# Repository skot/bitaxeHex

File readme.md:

Warning: the bitaxeHex is unfinished. there may be hardware and firmware bugs. Please see The bitaxeHex channel on the [OSMU Discord](https://discord.gg/osmu) for the latest status

> Closed Source is Antithetical to Bitcoin

# Presenting: The bitaxeHex
bitaxeHex is a follow on to the [bitaxe](https://github.com/skot/bitaxe) that incorporates six BM1366 ASICs from the Antminer S19XP

## Goals
- **Standalone**: can mine directly to your pool over WiFi. No External computer needed.
- **Embedded**: low cost, low maintenance, high availability, high reliability, low power.
- **ASIC**: based on the very efficient BM1366 from Bitmain.
- **Versatile**: solo/pool mining, autotune power/heat/efficiency.
- **Open Source**: All design files are provided.

## Features
- **ESP32-S3-WROOM-1** wifi microcontroller on board
- **TI TPS546D24ARVFR** buck regulator steps down the 12V input to power the chain of BM1366
- **TMP1075** measures inlet and outlet PCB temperature.
- **Microchip EMC2302** Controls dual fans
- Header for optional status LCD

## BM1366
- The BM1366 is a undocumented SHA256 mining ASIC from Bitmain. It's mostly used in the Antminer S19XP and S19K Pro
- Bitmain claims the BM1366 has 21.5 W/TH efficiency
- The BM1366 is available (new) for around $15 each.

## Current Status
- v304 This is going to be the official release candidate, but boards have not been produced yet, this version is not final.
- Power draw is around 50W @12V.
- ESP32 miner firmware will configure the power supply to run at the proper voltage.
- This is an _advanced_ build! If you don't have experience building boards, you should probably go build a single ASIC bitaxe first to get the technique down.

## Notes
- Beware that overclocking doesn't produce a higher hash rate on this board, it only causes more heat generation.
- If you decide to build a pre-release board, be sure to order 2 oz. copper on both the internal and external layers.
- The recommended heatsink is not anodized and very conductive on all surfaces. This _should_ be OK as the ASIC tops are not known to be conductive, but this needs some more investigation.

## Revision List
- v304 is a work in progress, some capacitor changes, additional features
- v303 has some improvements in the layout and the 33R inline resistors have been removed.
- V302 is the current working version of this board.  If you want to build this, pull down this git tag.
- V301 does not work, the power supply maintains voltage, but overheats in a drastic way
- V300 does not work, the power supply cannot maintain voltage when a load is applied

## Hardware
- [BM1366 from NBTC on AliExpress](https://www.aliexpress.us/item/3256803471845503.html). Both the `AL` and `AG` variants have been known to work.
- [Heatsink](https://www.aliexpress.us/item/3256805608902122.html) 90mm long variant. This will need to have threaded M3 mounting holes added. See the KiCad board file for the pattern
- [Fans](https://www.amazon.com/Noctua-NF-A8-PWM-Premium-Quiet/dp/B00NEMG62M) At least one 80x80mm 12V 4-pin fan. Like the Noctua NF-A8 PWM. Possibly two.
- [Enclosure](https://www.aliexpress.us/item/3256806064761702.html) (several sellers) 130mm long variant. The bitaxeHex needs to be run inside an enclosure to force air through the heatsink and effectively cool the BM1366s
- The TPS546 can potentially benefit from a [small self-adhesive heatsink](https://www.amazon.com/gp/product/B093V6RK58/) on the top of the package.
- All of the parts on the board are listed in the KiCad BOM

## Software
- [ESP-Miner-multichip](https://github.com/bitaxeorg/esp-miner-multichip) a fork of esp-miner to support multiple ASICs like on the bitaxeHex.

## Power Supply Requirements
- bitaxeHex takes 12V DC input via screw terminals. Power supply should be capable of 100W
  - This [120W Brick](https://www.amazon.com/gp/product/B07PWZQ33N) technically works, but gets a little warmer than it should. You'll need to change the end.
  - 12V 15A 110V AliExpress [Bare PSU](https://www.aliexpress.us/item/3256805439916551.html)

## Building
- Check out [building.md](building.md) for PCB ordering tips
- Check out [assembly.md](assembly.md) for assembly tips

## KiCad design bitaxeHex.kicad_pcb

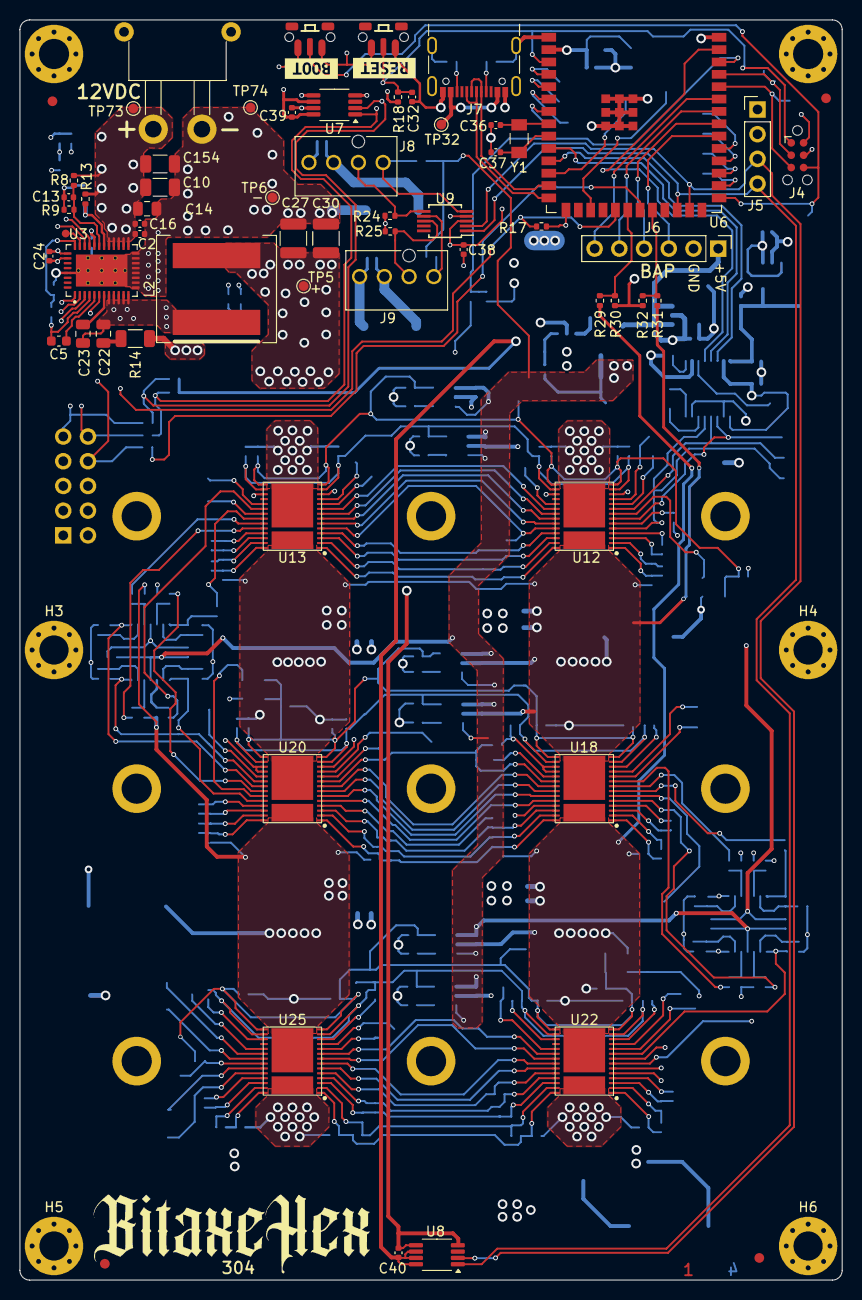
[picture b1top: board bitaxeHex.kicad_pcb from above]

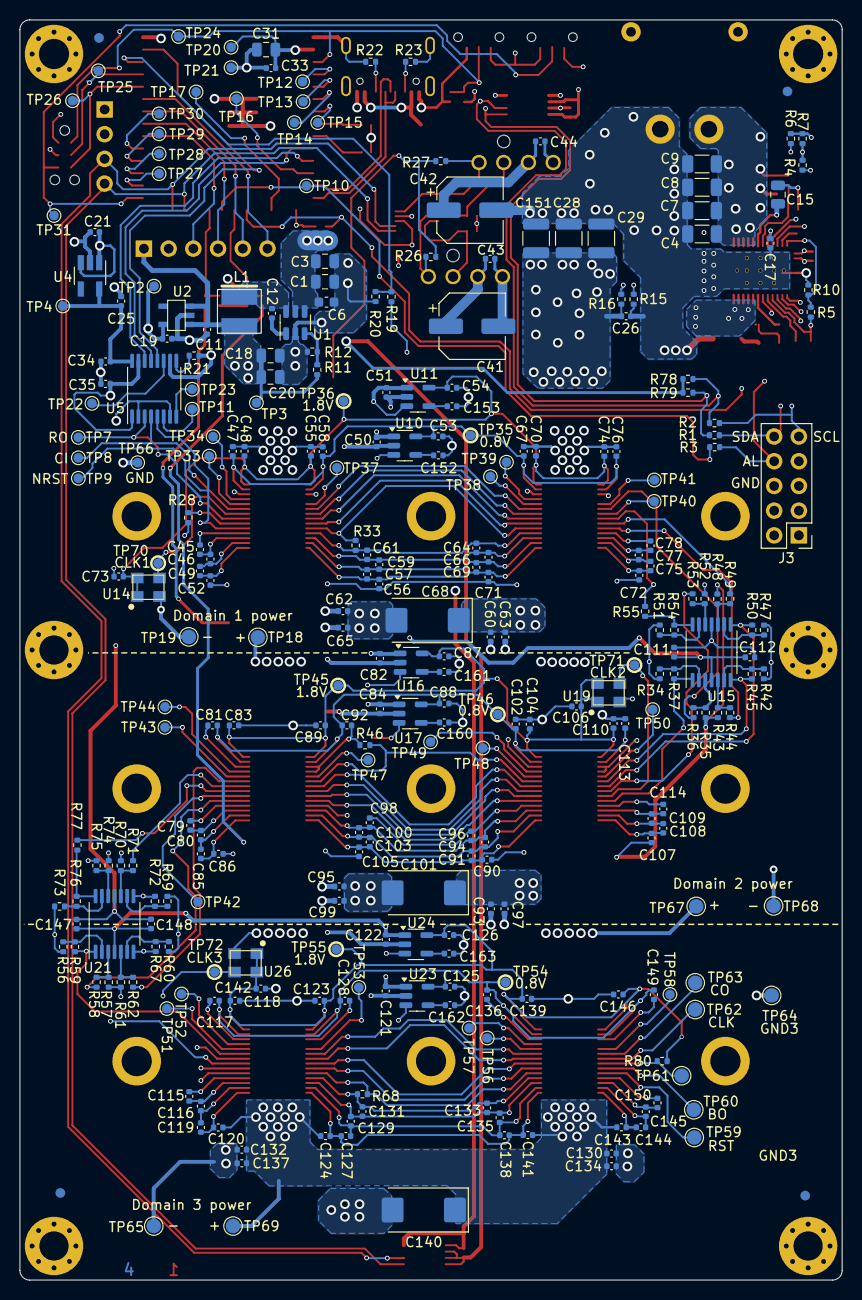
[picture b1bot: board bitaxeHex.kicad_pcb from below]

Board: 4 copper layers, 84.5 x 129.5 mm, 369 parts (289 on the bottom side), 191 nets.

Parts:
C1, C3, C18, C20, C31: 10uF; C_0805_2012Metric
C2: 4.7nF; C_0402_1005Metric
C4, C7, C8, C10: 22uF; C_1206_3216Metric
C5: 1uF; C_0603_1608Metric
C6: 0.1uF; C_0603_1608Metric
C9, C154: 47uF; C_1206_3216Metric
C11, C19, C21, C25, C32, C45, C46, C47, C48, C49, C52, C53, C54, C55, C56, C57, C58, C59, C61, C63, C64, C65, C66, C67, C69, C70, C71, C72, C74, C75, C76, C77, C78, C79, C80, C81, C83, C85, C86, C87, C88, C89, C90, C91, C92, C94, C96, C97, C98, C99, C100, C102, C103, C104, C105, C107, C108, C109, C110, C112, C113, C114, C115, C116, C117, C118, C119, C120, C123, C124, C125, C126, C127, C128, C129, C131, C133, C134, C135, C136, C137, C138, C139, C141, C143, C144, C145, C146, C148, C149, C150: 1uF; C_0402_1005Metric
C12, C33, C50, C51, C60, C62, C73, C82, C84, C93, C95, C106, C111, C121, C122, C130, C132, C142, C147: 0.1uF; C_0402_1005Metric
C13: 100nF; C_0402_1005Metric
C14, C15: 1uF; C_0805_2012Metric
C16, C26: 2.2nF; C_0402_1005Metric
C17: 4.7uF; C_0402_1005Metric
C22: 1nF; C_0805_2012Metric
C23: 100nF; C_0805_2012Metric
C24: 100pF; C_0402_1005Metric
C27, C28, C29: 47uF; C_1210_3225Metric
C30, C151: 100uF; C_1210_3225Metric
C34, C35, C38, C39, C40, C43, C44: 311-3342-1-ND; C_0402_1005Metric
C36, C37: 6.8pF; C_0402_1005Metric
C41, C42: 220uF; CP_Elec_6.3x7.7
C68, C101, C140: 330uF; CP_EIA-7343-31_Kemet-D_Pad2.25x2.55mm_HandSolder
C152, C153, C160, C161, C162, C163: 0.01uF; C_0402_1005Metric
FID1, FID2, FID3, FID4, FID5, FID6, FID7, FID8: Fiducial; Fiducial_1mm_Mask2mm
H1, H2, H3, H4, H5, H6: MountingHole; MountingHole_3mm_Pad_Via
H7, H8, H9, H10, H11, H12, H13, H14, H15: HeatsinkMountingHole; 3.1mm_mounting
HS1: Heatsink; hex-heatsink
J1: XT30; XT30PW-M
J3: Conn_02x05_Odd_Even; PinHeader_2x05_P2.54mm_Vertical
J4: TC2030-IDC; Tag-Connect_TC2030-IDC-NL_2x03_P1.27mm_Vertical
J5: Conn_01x04; PinHeader_1x04_P2.54mm_Vertical
J6: Conn_01x06; PinHeader_1x06_P2.54mm_Vertical
J7: USB_C_Receptacle_USB2.0; USB_C_Receptacle_GCT_USB4105-xx-A_16P_TopMnt_Horizontal
J8, J9: Conn_01x04; 470531000
L1: 8.2 uH; 74438357082
L2: 680nH; L_Coilcraft_XAL1010-XXX
R1, R2, R3: 0R; R_0402_1005Metric
R4, R5: 17.8K; R_0402_1005Metric
R6, R17, R18, R26, R27, R28, R35, R36, R43, R44, R48, R49, R52, R53, R57, R58, R61, R62, R70, R71, R74, R75: 10k; R_0402_1005Metric
R7: 31.6K; R_0402_1005Metric
R8: 12.7K; R_0402_1005Metric
R9, R16: 1.37K; R_0402_1005Metric
R10: 26.1K; R_0402_1005Metric
R11: 115k; R_0402_1005Metric
R12, R20, R30, R32: 22.1k; R_0402_1005Metric
R13: 10R; R_0402_1005Metric
R14: 1R; R_1206_3216Metric
R15: 49.9R; R_0402_1005Metric
R19, R29, R31: 7.87k; R_0402_1005Metric
R21: 20k; R_0402_1005Metric
R22, R23, R78, R79: 5.1k; R_0402_1005Metric
R24, R25: 5.6k; R_0402_1005Metric
R33, R46, R68: 2k; R_0402_1005Metric
R34, R37, R42, R45, R47, R50, R51, R54, R55, R56, R59, R60, R67, R69, R72, R73, R76, R77, R80: 1k; R_0402_1005Metric
SW1, SW2: SWITCH-SPST; TL3340-switch
TP1: TestPoint; TestPoint_Pad_D0.8mm
TP2, TP3, TP4, TP5, TP6, TP7, TP8, TP9, TP10, TP11, TP12, TP13, TP14, TP15, TP16, TP17, TP20, TP21, TP22, TP23, TP24, TP25, TP26, TP27, TP28, TP29, TP30, TP31, TP32, TP33, TP34, TP37, TP38, TP39, TP40, TP41, TP42, TP43, TP44, TP47, TP48, TP49, TP50, TP51, TP52, TP53, TP56, TP57, TP58, TP66, TP73, TP74: TestPoint; TestPoint_Pad_D1.0mm
TP18, TP67, TP69: +; TestPoint_Pad_D1.5mm
TP19, TP65, TP68: -; TestPoint_Pad_D1.5mm
TP35, TP36, TP45, TP46, TP54, TP55, TP70, TP71, TP72: TestPoint; TestPoint_Pad_D1.0mm_highlight
TP59, TP60, TP61, TP62, TP63, TP64: TestPoint; TestPoint_Pad_D1.5mm
U1: LMR54410; SOT-23-6
U2: RT9080-33GJ5
U3: TPS546D24ARVFR; LQFN40-CLIP
U4: MIC5504; SOT-23-5_HandSoldering
U5: SN74AVC4T774; TSSOP-16_4.4x5mm_P0.65mm
U6: ESP32-S3-WROOM-1; ESP32-S3-WROOM-1U
U7, U8: TMP1075; HVSSOP-8_3x3mm_P0.65mm
U9: EMC2302; MSOP-10_3x3mm_P0.5mm
U10, U17, U23: SGM2036-0v8; TSOT-23-5
U11, U16, U24: SGM2036-1v8; TSOT-23-5
U12, U13, U22, U25: BM1366_mode1; BM1366
U14, U19, U26: 25MHz; O 25,0-JO32-B-1V3-1-T1-LF
U15, U21: TLV3544; TSSOP-14_4.4x5mm_P0.65mm
U18, U20: BM1366_mode0; BM1366
Y1: 32.768kHz; SC32S-7PF20PPM
kibuzzard-65356D4E: G***; kibuzzard-65356D4E
kibuzzard-65356D5C: G***; kibuzzard-65356D5C

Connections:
/1V8: C25.1, C34.2, TP4.1 (1_1), U4.5 (VOUT), U5.16 (VCCA)
/3V3: C19.1, C21.1, C31.1, C33.1, C35.1, C38.1, C39.1, C40.1, J4.2, J5.2, R17.2, R18.1, R24.2, R25.2, R78.2, R79.1, TP2.1 (1_1), TP20.1 (1_1), U2.5 (VOUT), U4.1 (VIN), U4.3 (EN), U5.1 (DIR1), U5.15 (VCCB), U6.2 (3V3), U6.15 (GPIO3/TOUCH3/ADC1_CH2*), U7.6 (A1), U7.8 (V+), U8.6 (A1), U8.7 (A0), U8.8 (V+), U9.3 (VDD)
/5V: C11.1, C18.1, C20.1, C50.2, C51.2, C82.2, C84.2, C111.2, C112.2, C121.2, C122.2, C147.2, C148.2, J6.1, L1.2, R11.1, R26.2, R27.2, TP3.1 (1_1), U2.1 (VIN), U2.3 (EN), U10.1 (VIN), U10.3 (EN), U11.1 (VIN), U11.3 (EN), U15.4 (V+), U16.1 (VIN), U16.3 (EN), U17.1 (VIN), U17.3 (EN), U21.4 (V+), U23.1 (VIN), U23.3 (EN), U24.1 (VIN), U24.3 (EN)
/BM1366-1/0V8: C47.1, C53.1, C58.1, C67.1, C76.1, TP35.1 (1_1), U10.5 (VOUT), U12.13 (VDDIO_08_0), U12.16 (VDDIO_08_1), U13.13 (VDDIO_08_0), U13.16 (VDDIO_08_1)
/BM1366-1/1V8: C48.1, C54.1, C55.1, C70.1, C73.1, C74.1, TP36.1 (1_1), U11.5 (VOUT), U12.14 (VDDIO_18_0), U12.15 (VDDIO_18_1), U13.14 (VDDIO_18_0), U13.15 (VDDIO_18_1), U14.1 (EN), U14.4 (VIN)
/BM1366-1/BI1: R28.2, U12.6 (BI)
/BM1366-1/BO: R49.1, U13.23 (BO)
/BM1366-1/CLKI1: TP70.1 (1_1), U12.8 (CLKI), U14.3 (OUT)
/BM1366-1/CO: R36.1, U13.20 (CO)
/BM1366-1/NRSTO: R44.1, U13.24 (NRSTO)
/BM1366-1/RI: R55.1, U13.22 (RI)
/BM1366-2/0V8: C81.1, C88.1, C92.1, C102.1, C113.1, TP46.1 (1_1), U17.5 (VOUT), U18.13 (VDDIO_08_0), U18.16 (VDDIO_08_1), U20.13 (VDDIO_08_0), U20.16 (VDDIO_08_1)
/BM1366-2/1V8: C83.1, C87.1, C89.1, C104.1, C106.1, C110.1, TP45.1 (1_1), U16.5 (VOUT), U18.14 (VDDIO_18_0), U18.15 (VDDIO_18_1), U19.1 (EN), U19.4 (VIN), U20.14 (VDDIO_18_0), U20.15 (VDDIO_18_1)
/BM1366-2/BI2: R50.1, U15.8, U20.21 (BI)
/BM1366-2/BO: R71.1, U18.8 (BO)
/BM1366-2/CI2: R37.1, U15.1, U20.24 (CI)
/BM1366-2/CLKI2: TP71.1 (1_1), U19.3 (OUT), U20.23 (CLKI)
/BM1366-2/CO: R58.1, U18.5 (CO)
/BM1366-2/NRSTI2: R45.1, U15.7, U20.20 (NRSTI)
/BM1366-2/NRSTO: R62.1, U18.9 (NRSTO)
/BM1366-2/RI: R77.1, U18.7 (RI)
/BM1366-2/RO2: R53.1, U20.22 (RO)
/BM1366-3/0V8: C117.1, C125.1, C128.1, C136.1, C149.1, TP54.1 (1_1), U22.13 (VDDIO_08_0), U22.16 (VDDIO_08_1), U23.5 (VOUT), U25.13 (VDDIO_08_0), U25.16 (VDDIO_08_1)
/BM1366-3/1V8: C118.1, C123.1, C126.1, C139.1, C142.1, C146.1, R80.1, TP55.1 (1_1), U22.14 (VDDIO_18_0), U22.15 (VDDIO_18_1), U24.5 (VOUT), U25.14 (VDDIO_18_0), U25.15 (VDDIO_18_1), U26.1 (EN), U26.4 (VIN)
/BM1366-3/BI3: R72.1, U21.8, U22.6 (BI)
/BM1366-3/BO3: TP60.1 (1_1), U25.23 (BO)
/BM1366-3/CI3: R59.1, U21.1, U22.9 (CI)
/BM1366-3/CLKI3: TP72.1 (1_1), U22.8 (CLKI), U26.3 (OUT)
/BM1366-3/CLKO3: TP62.1 (1_1), U25.21 (CLKO)
/BM1366-3/CO3: TP63.1 (1_1), U25.20 (CO)
/BM1366-3/NRSTI3: R67.1, U21.7, U22.5 (NRSTI)
/BM1366-3/NRSTO3: TP59.1 (1_1), U25.24 (NRSTO)
/BM1366-3/RI3: R80.2, TP61.1 (1_1), U25.22 (RI)
/BM1366-3/RO3: R75.1, U22.7 (RO)
/CI: TP8.1 (1_1), U5.4 (A2), U12.9 (CI)
/ESP32/ASIC_RST: U5.12 (B3), U6.39 (GPIO1/TOUCH1/ADC1_CH0)
/ESP32/EN: C32.1, J4.1, R18.2, SW1.2, TP24.1 (1_1), U6.3 (EN)
/ESP32/ESP32_RX: U5.14 (B1), U6.11 (GPIO18/U1RXD/ADC2_CH7/CLK_OUT3)
/ESP32/ESP32_TX: U5.13 (B2), U6.10 (GPIO17/U1TXD/ADC2_CH6)
/ESP32/IO0: J4.6, SW2.2, TP31.1 (1_1), U6.27 (GPIO0/BOOT*)
/ESP32/P_RX: J4.5, TP26.1 (1_1), U6.36 (U0RXD/GPIO44/CLK_OUT2)
/ESP32/P_TX: J4.3, TP25.1 (1_1), U6.37 (U0TXD/GPIO43/CLK_OUT1)
/ESP32/VDD1_SAMPLE: R31.1, R32.2, U6.22 (GPIO14/TOUCH14/ADC2_CH3/FSPIWP/FSPIDQS/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)
/ESP32/VDD2_SAMPLE: R29.1, R30.2, U6.20 (GPIO12/TOUCH12/ADC2_CH1/FSPICLK/FSPIIO6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)
/ESP32/VDD3_SAMPLE: R19.1, R20.2, U6.38 (GPIO2/TOUCH2/ADC1_CH1)
/ESP32/XIN32: C36.1, U6.8 (GPIO15/U0RTS/ADC2_CH4/XTAL_32K_P), Y1.1
/ESP32/XOUT32: C37.1, U6.9 (GPIO16/U0CTS/ADC2_CH5/XTAL_32K_NH5), Y1.2
/Fan/FAN1_PWM: J8.4, R27.1, U9.5 (PWM1)
/Fan/FAN1_TACH: J8.3, R24.1, U9.6 (TACH1)
/Fan/FAN2_PWM: J9.4, R26.1, U9.7 (PWM2)
/Fan/FAN2_TACH: J9.3, R25.1, U9.8 (TACH2)
/NRSTI: TP9.1 (1_1), U5.5 (A3), U12.5 (NRSTI)
/Power/PGOOD: R17.1, U3.1 (PGD), U6.19 (GPIO11/TOUCH11/ADC2_CH0/FSPID/FSPIIO5/S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)
/Power/PMB_ALRT: J3.8, R3.2, U3.6 (SMB_ALRT)
/Power/PMB_SCL: J3.9, R2.2, U3.3 (PMB_CLK)
/Power/PMB_SDA: J3.10, R1.2, U3.2 (PMB_DATA)
/Power/SW: C22.1, C23.2, L2.1, U3.8 (SW), U3.9 (SW), U3.10 (SW), U3.11 (SW), U3.12 (SW)
/RO: TP7.1 (1_1), U5.3 (A1), U12.7 (RO)
/SCL: J5.3, R2.1, R78.1, U6.25 (GPIO48/SPICLK_N/SUBSPICLK_N_DIFF), U7.2 (SCL), U8.2 (SCL), U9.2 (SMCLK)
/SDA: J5.4, R1.1, R79.2, U6.24 (GPIO47/SPICLK_P/SUBSPICLK_P_DIFF), U7.1 (SDA), U8.1 (SDA), U9.1 (SMDATA)
/SMB_ALRT: R3.1, TP10.1 (1_1), U6.21 (GPIO13/TOUCH13/ADC2_CH2/FSPIQ/FSPIIO7/S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)
/VDD: C26.1, C27.1, C28.1, C29.1, C30.1, C120.2, C124.1, C130.2, C132.2, C134.1, C137.1, C140.1, C141.2, C143.1, C151.1, L2.2, R16.1, R19.2, R57.1, R61.1, R70.1, TP5.1 (1_1), TP69.1 (1_1), U22.29 (VDD), U25.29 (VDD)
/VDD1: C52.2, C56.1, C60.2, C62.2, C63.1, C65.1, C68.1, C71.2, C72.1, C79.1, C81.2, C82.1, C83.2, C84.1, C87.2, C88.2, C89.2, C92.2, C93.1, C95.1, C96.2, C97.2, C98.1, C99.2, C101.2, C102.2, C104.2, C106.2, C110.2, C113.2, C114.2, C160.2, C161.2, R31.2, R34.2, R42.2, R46.1, R47.2, R51.2, R74.1, TP18.1 (1_1), TP68.1 (1_1), U12.29 (VDD), U13.29 (VDD), U16.2 (GND), U17.2 (GND), U18.4 (VSS), U18.12 (PLL_VSS), U18.17 (VSS), U18.18 (PIN_MODE), U18.25 (VSS), U18.30 (VSS), U19.2 (GND), U20.4 (VSS), U20.12 (PLL_VSS), U20.17 (VSS), U20.18 (PIN_MODE), U20.25 (VSS), U20.30 (VSS)
/VDD2: C86.2, C90.1, C93.2, C95.2, C97.1, C99.1, C101.1, C105.2, C107.1, C115.1, C117.2, C118.2, C121.1, C122.1, C123.2, C125.2, C126.2, C128.2, C130.1, C131.2, C132.1, C133.1, C134.2, C136.2, C137.2, C139.2, C140.2, C142.2, C146.2, C149.2, C150.2, C162.2, C163.2, R29.2, R35.2, R43.1, R48.1, R56.2, R60.2, R68.1, R69.2, R73.2, TP64.1 (1_1), TP65.1 (1_1), TP67.1 (1_1), U18.29 (VDD), U20.29 (VDD), U22.4 (VSS), U22.12 (PLL_VSS), U22.17 (VSS), U22.25 (VSS), U22.30 (VSS), U23.2 (GND), U24.2 (GND), U25.4 (VSS), U25.12 (PLL_VSS), U25.17 (VSS), U25.25 (VSS), U25.30 (VSS), U26.2 (GND)
/VIN: C1.1, C2.1, C3.1, C4.1, C6.2, C7.1, C8.1, C9.1, C10.1, C14.1, C16.1, C41.1, C42.1, C43.1, C44.1, C154.1, J1.1 (+V), J8.2, J9.2, R8.1, R13.1, TP73.1 (1_1), U1.4 (EN), U1.5 (VIN), U3.21 (PVIN), U3.22 (PVIN), U3.23 (PVIN), U3.24 (PVIN), U3.25 (PVIN)
GND: C1.2, C2.2, C3.2, C4.2, C6.1, C7.2, C8.2, C9.2, C10.2, C11.2, C13.2, C14.2, C15.1, C16.2, C17.2, C18.2, C19.2, C20.2, C21.2, C25.2, C26.2, C27.2, C28.2, C29.2, C30.2, C31.2, C32.2, C33.2, C34.1, C35.2, C36.2, C37.2, C38.2, C39.2, C40.2, C41.2, C42.2, C43.2, C44.2, C45.1, C47.2, C48.2, C50.1, C51.1, C53.2, C54.2, C55.2, C58.2, C60.1, C61.2, C62.1, C63.2, C64.1, C65.2, C67.2, C68.2, C70.2, C73.2, C74.2, C76.2, C78.2, C111.1, C112.1, C147.1, C148.1, C151.2, C152.2, C153.2, C154.2, H1.1 (1_1), H2.1 (1_1), J1.2 (GND), J3.6, J4.4, J5.1, J6.2, J7.A1 (GND), J7.A12 (GND), J7.B1 (GND), J7.B12 (GND), J7.S1 (SHIELD), J8.1, J9.1, R6.1, R7.2, R9.2, R10.2, R12.2, R14.2, R15.2, R20.1, R21.1, R22.1, R23.1, R28.1, R30.1, R32.1, R33.1, R52.1, SW1.1, SW2.1, TP6.1 (1_1), TP19.1 (1_1), TP21.1 (1_1), TP66.1 (1_1), TP74.1 (1_1), U1.2 (GND), U2.2 (GND), U3.13 (PGND), U3.14 (PGND), U3.15 (PGND), U3.16 (PGND), U3.17 (PGND), U3.18 (PGND), U3.19 (PGND), U3.20 (PGND), U3.37 (AGND), U3.41 (PAD), U4.2 (GND), U5.2 (DIR2), U5.7 (DIR3), U5.10 (GND), U6.1 (GND), U6.40 (GND), U6.41 (GND), U7.4 (GND), U7.5 (A2), U7.7 (A0), U8.4 (GND), U8.5 (A2), U9.4 (GND), U10.2 (GND), U11.2 (GND), U12.4 (VSS), U12.12 (PLL_VSS), U12.17 (VSS), U12.25 (VSS), U12.30 (VSS), U13.4 (VSS), U13.12 (PLL_VSS), U13.17 (VSS), U13.25 (VSS), U13.30 (VSS), U14.2 (GND), U15.11 (V-), U21.11 (V-)
unnamed: C22.2, R14.1
unnamed: J6.3, U6.32 (MTCK/GPIO39/CLK_OUT3/SUBSPICS1)
unnamed: J6.4, U6.33 (MTDO/GPIO40/CLK_OUT2)
unnamed: J6.5, U6.34 (MTDI/GPIO41/CLK_OUT1)
unnamed: J6.6, U6.35 (MTMS/GPIO42)
unnamed: J7.A5 (CC1), R22.2
unnamed: J7.B5 (CC2), R23.2
unnamed: J7.A4 (VBUS), J7.A9 (VBUS), J7.B4 (VBUS), J7.B9 (VBUS), TP32.1 (1_1)
unnamed: R54.1, R55.2, U15.14
unnamed: R76.1, R77.2, U21.14
unnamed: C12.2, U1.1 (CB)
unnamed: R11.2, R12.1, U1.3 (FB)
unnamed: C12.1, L1.1, U1.6 (SW)
unnamed: TP1.1 (1_1), U3.31 (ADRSEL)
unnamed: C15.2, R13.2, U3.26 (AVIN)
unnamed: C23.1, U3.7 (BOOT)
unnamed: C5.1, R4.1, R5.1, U3.4 (BP1V5)
unnamed: C5.2, U3.5 (DRTN)
unnamed: C13.1, R8.2, R9.1, U3.27 (EN/UVLO)
unnamed: C24.2, R15.1, U3.34 (GOSNS)
unnamed: R5.2, R10.1, U3.32 (MSEL1)
unnamed: R6.2, U3.29 (MSEL2)
unnamed: C17.1, U3.28 (VDD5)
unnamed: C24.1, R16.2, U3.33 (VOSNS)
unnamed: R4.2, R7.1, U3.30 (VSEL)
unnamed: TP11.1 (1_1), U5.6 (A4)
unnamed: TP22.1 (1_1), U5.11 (B4)
unnamed: TP23.1 (1_1), U5.8 (DIR4)
unnamed: R21.2, U5.9 (OE)
unnamed: TP12.1 (1_1), U6.4 (GPIO4/TOUCH4/ADC1_CH3)
unnamed: TP13.1 (1_1), U6.5 (GPIO5/TOUCH5/ADC1_CH4)
unnamed: TP14.1 (1_1), U6.6 (GPIO6/TOUCH6/ADC1_CH5)
unnamed: TP15.1 (1_1), U6.7 (GPIO7/TOUCH7/ADC1_CH6)
unnamed: TP16.1 (1_1), U6.12 (GPIO8/TOUCH8/ADC1_CH7/SUBSPICS1)
unnamed: TP17.1 (1_1), U6.17 (GPIO9/TOUCH9/ADC1_CH8/FSPIHD/SUBSPIHD)
unnamed: J7.A7 (D-), J7.B7 (D-), U6.13 (GPIO19/U1RTS/ADC2_CH8/CLK_OUT2/USB_D-)
unnamed: J7.A6 (D+), J7.B6 (D+), U6.14 (GPIO20/U1CTS/ADC2_CH9/CLK_OUT1/USB_D+)
unnamed: TP30.1 (1_1), U6.31 (GPIO38/FSPIWP/SUBSPIWP)
unnamed: TP29.1 (1_1), U6.30 (SPIDQS/GPIO37/FSPIQ/SUBSPIQ)
unnamed: TP27.1 (1_1), U6.28 (SPIIO6/GPIO35/FSPID/SUBSPID)
unnamed: TP28.1 (1_1), U6.29 (SPIIO7/GPIO36/FSPICLK/SUBSPICLK)
unnamed: C152.1, U10.4 (BP)
unnamed: C153.1, U11.4 (BP)
unnamed: TP33.1 (1_1), U12.10 (ADDR0)
unnamed: TP34.1 (1_1), U12.11 (ADDR1)
unnamed: U12.23 (BO), U13.6 (BI)
unnamed: U12.21 (CLKO), U13.8 (CLKI)
unnamed: U12.20 (CO), U13.9 (CI)
unnamed: TP37.1 (1_1), U12.19 (INV_CLKO)
unnamed: R33.2, U12.24 (NRSTO), U13.5 (NRSTI)
unnamed: U12.22 (RI), U13.7 (RO)
unnamed: C49.2, C52.1, U12.1 (VDD1_0)
unnamed: C56.2, C57.1, C69.2, C71.1, U12.28 (VDD1_1), U13.1 (VDD1_0)
unnamed: C46.2, C49.1, U12.2 (VDD2_0)
unnamed: C57.2, C59.1, C66.2, C69.1, U12.27 (VDD2_1), U13.2 (VDD2_0)
unnamed: C45.2, C46.1, U12.3 (VDD3_0)
unnamed: C59.2, C61.1, C64.2, C66.1, U12.26 (VDD3_1), U13.3 (VDD3_0)
unnamed: TP38.1 (1_1), U13.10 (ADDR0)
unnamed: TP39.1 (1_1), U13.11 (ADDR1)
unnamed: TP40.1 (1_1), U13.21 (CLKO)
unnamed: TP41.1 (1_1), U13.19 (INV_CLKO)
unnamed: C72.2, C75.1, U13.28 (VDD1_1)
unnamed: C75.2, C77.1, U13.27 (VDD2_1)
unnamed: C77.2, C78.1, U13.26 (VDD3_1)
unnamed: R35.1, R36.2, U15.3 (+)
unnamed: R34.1, R37.2, U15.2 (-)
unnamed: R43.2, R44.2, U15.5 (+)
unnamed: R42.1, R45.2, U15.6 (-)
unnamed: R48.2, R49.2, U15.10 (+)
unnamed: R47.1, R50.2, U15.9 (-)
unnamed: R52.2, R53.2, U15.12 (+)
unnamed: R51.1, R54.2, U15.13 (-)
unnamed: C161.1, U16.4 (BP)
unnamed: C160.1, U17.4 (BP)
unnamed: TP43.1 (1_1), U18.10 (ADDR0)
unnamed: TP44.1 (1_1), U18.11 (ADDR1)
unnamed: U18.21 (BI), U20.8 (BO)
unnamed: U18.24 (CI), U20.5 (CO)
unnamed: U18.23 (CLKI), U20.6 (CLKO)
unnamed: TP42.1 (1_1), U18.6 (CLKO)
unnamed: TP47.1 (1_1), U18.19 (INV_CLKO)
unnamed: R46.2, U18.20 (NRSTI), U20.9 (NRSTO)
unnamed: U18.22 (RO), U20.7 (RI)
unnamed: C79.2, C80.1, U18.3 (VDD1_0)
unnamed: C94.2, C96.1, C98.2, C100.1, U18.26 (VDD1_1), U20.3 (VDD1_0)
unnamed: C80.2, C85.1, U18.2 (VDD2_0)
unnamed: C91.2, C94.1, C100.2, C103.1, U18.27 (VDD2_1), U20.2 (VDD2_0)
unnamed: C85.2, C86.1, U18.1 (VDD3_0)
unnamed: C90.2, C91.1, C103.2, C105.1, U18.28 (VDD3_1), U20.1 (VDD3_0)
unnamed: TP48.1 (1_1), U20.10 (ADDR0)
unnamed: TP49.1 (1_1), U20.11 (ADDR1)
unnamed: TP50.1 (1_1), U20.19 (INV_CLKO)
unnamed: C109.2, C114.1, U20.26 (VDD1_1)
unnamed: C108.2, C109.1, U20.27 (VDD2_1)
unnamed: C107.2, C108.1, U20.28 (VDD3_1)
unnamed: R57.2, R58.2, U21.3 (+)
unnamed: R56.1, R59.2, U21.2 (-)
unnamed: R61.2, R62.2, U21.5 (+)
unnamed: R60.1, R67.2, U21.6 (-)
unnamed: R70.2, R71.2, U21.10 (+)
unnamed: R69.1, R72.2, U21.9 (-)
unnamed: R74.2, R75.2, U21.12 (+)
unnamed: R73.1, R76.2, U21.13 (-)
unnamed: TP51.1 (1_1), U22.10 (ADDR0)
unnamed: TP52.1 (1_1), U22.11 (ADDR1)
unnamed: U22.23 (BO), U25.6 (BI)
unnamed: U22.21 (CLKO), U25.8 (CLKI)
unnamed: U22.20 (CO), U25.9 (CI)
unnamed: TP53.1 (1_1), U22.19 (INV_CLKO)
unnamed: R68.2, U22.24 (NRSTO), U25.5 (NRSTI)
unnamed: U22.22 (RI), U25.7 (RO)
unnamed: C119.2, C120.1, U22.1 (VDD1_0)
unnamed: C124.2, C127.1, C138.2, C141.1, U22.28 (VDD1_1), U25.1 (VDD1_0)
unnamed: C116.2, C119.1, U22.2 (VDD2_0)
unnamed: C127.2, C129.1, C135.2, C138.1, U22.27 (VDD2_1), U25.2 (VDD2_0)
unnamed: C115.2, C116.1, U22.3 (VDD3_0)
unnamed: C129.2, C131.1, C133.2, C135.1, U22.26 (VDD3_1), U25.3 (VDD3_0)
unnamed: C162.1, U23.4 (BP)
unnamed: C163.1, U24.4 (BP)
unnamed: TP56.1 (1_1), U25.10 (ADDR0)
unnamed: TP57.1 (1_1), U25.11 (ADDR1)
unnamed: TP58.1 (1_1), U25.19 (INV_CLKO)
unnamed: C143.2, C144.1, U25.28 (VDD1_1)
unnamed: C144.2, C145.1, U25.27 (VDD2_1)
unnamed: C145.2, C150.1, U25.26 (VDD3_1)

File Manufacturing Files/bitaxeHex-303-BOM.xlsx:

| Bitaxe Hex v303 BOM
 | Qty | Reference | Value | Footprint | DK | PARTNO
 | 5 | C1, C3, C18, C20, C31 | 10uF | Capacitor_SMD:C_0805_2012Metric | 490-18664-1-ND | GRM21BR61H106ME43L
 | 1 | C2 | 4.7nF | Capacitor_SMD:C_0402_1005Metric | 490-1309-1-ND | GRM155R71E472KA01D
 | 4 | C4, C7, C8, C9 | 22uF | Capacitor_SMD:C_1210_3225Metric | 490-3889-1-ND | GRM32ER61E226KE15L
 | 1 | C5 | 1uF | Capacitor_SMD:C_0603_1608Metric | 490-1550-1-ND | GRM188R60J105KA01D
 | 1 | C6 | 0.1uF | Capacitor_SMD:C_0603_1608Metric | 478-KGM15BR71H104KTCT-ND | KGM15BR71H104KT
 | 2 | C10, C30 | 180uF | Capacitor_SMD:CP_Elec_6.3x5.9 | P16479CT-ND | 16SVPF180M
 | 91 | C11, C19, C21, C25, C32, C45, C46, C47, C48, C49, C52, C53, C54, C55, C56, C57,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 | 1uF | Capacitor_SMD:C_0402_1005Metric | 587-5514-1-ND | EMK105BJ105MV-F
 | 19 | C12, C33, C50, C51, C60, C62, C73, C82, C84, C93, C95, C106, C111, C121, C122, 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 | 0.1uF | Capacitor_SMD:C_0402_1005Metric | 478-KGM05AR71C104KHCT-ND | KGM05AR71C104KH
 | 1 | C13 | 100nF | Capacitor_SMD:C_0402_1005Metric | 490-6321-1-ND | GRM155R71A104KA01D
 | 2 | C14, C15 | 1uF | Capacitor_SMD:C_0805_2012Metric | 587-1291-1-ND | TMK212BJ105KG-T
 | 2 | C16, C26 | 2.2nF | Capacitor_SMD:C_0402_1005Metric | 490-8257-1-ND | GRM155R61H222KA01D
 | 1 | C17 | 4.7uF | Capacitor_SMD:C_0402_1005Metric | 490-14306-1-ND | GRM155R61A475MEAAD
 | 1 | C22 | 1nF | Capacitor_SMD:C_0805_2012Metric | 311-1127-1-ND | CC0805KRX7R9BB102
 | 1 | C23 | 100nF | Capacitor_SMD:C_0805_2012Metric | 478-KGM21NR71E104KTCT-ND | KGM21NR71E104KT
 | 1 | C24 | 100pF | Capacitor_SMD:C_0402_1005Metric | 732-7431-1-ND | 885012005013
 | 3 | C27, C28, C29 | 47uF | Capacitor_SMD:C_1210_3225Metric | 490-6539-1-ND | GRM32ER61C476KE15L
 | 7 | C34, C35, C38, C39, C40, C43, C44 | 311-3342-1-ND | Capacitor_SMD:C_0402_1005Metric | 478-KGM05AR71C104KHCT-ND | KGM05AR71C104KH
 | 2 | C41, C42 | 220uF | Capacitor_SMD:CP_Elec_6.3x7.7 | 732-8422-1-ND | 865080345012
 | 3 | C68, C101, C140 | 330uF | Capacitor_Tantalum_SMD:CP_EIA-7343-31_Kemet-D_Pad2.25x2.55mm_HandSolder | 718-1028-1-ND | 293D337X9010E2TE3
 | 3 | R1, R2, R3 | 0R | Resistor_SMD:R_0402_1005Metric | 311-0.0JRCT-ND | RC0402JR-070RL
 | 2 | R4, R5 | 17.8K | Resistor_SMD:R_0402_1005Metric | RMCF0402FT17K8CT-ND | RMCF0402FT17K8
 | 1 | R6 | 10K | Resistor_SMD:R_0402_1005Metric | RMCF0402FT10K0CT-ND | RMCF0402FT10K0
 | 1 | R7 | 31.6K | Resistor_SMD:R_0402_1005Metric | YAG3115CT-ND | RC0402FR-0731K6L
 | 1 | R8 | 12.7K | Resistor_SMD:R_0402_1005Metric | YAG2964CT-ND | RC0402FR-0712K7L
 | 2 | R9, R16 | 1.37K | Resistor_SMD:R_0402_1005Metric | YAG3035CT-ND | RC0402FR-071K37L
 | 1 | R10 | 26.1K | Resistor_SMD:R_0402_1005Metric | 311-26.1KLRCT-ND | RC0402FR-0726K1L
 | 10 | R11, R29, R30, R31, R38, R39, R41, R63, R64, R65 | 115k | Resistor_SMD:R_0402_1005Metric | YAG2956CT-ND | RC0402FR-07115KL
 | 2 | R12, R20 | 22.1k | Resistor_SMD:R_0402_1005Metric | 311-22.1KLRCT-ND | RC0402FR-0722K1L
 | 1 | R13 | 10R | Resistor_SMD:R_0402_1005Metric | 311-10.0LRCT-ND | RC0402FR-0710RL
 | 1 | R14 | 1R | Resistor_SMD:R_1206_3216Metric | CSR1206FT1R00CT-ND | CSR1206FT1R00
 | 1 | R15 | 49.9R | Resistor_SMD:R_0402_1005Metric | 311-49.9LRCT-ND | RC0402FR-0749R9L
 | 21 | R17, R18, R26, R27, R28, R35, R36, R43, R44, R48, R49, R52, R53, R57, R58, R61,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 | 10k | Resistor_SMD:R_0402_1005Metric | 311-10KJRCT-ND | RC0402JR-0710KL
 | 1 | R19 | 7.87k | Resistor_SMD:R_0402_1005Metric | 311-7.87KLRCT-ND | RC0402FR-077K87L
 | 1 | R21 | 20k | Resistor_SMD:R_0402_1005Metric | 311-20.0KLRCT-ND | RC0402FR-0720KL
 | 2 | R22, R23 | 5.1k | Resistor_SMD:R_0402_1005Metric | 13-RC0402FR-135K1LCT-ND | RC0402FR-135K1L
 | 2 | R24, R25 | 5.6k | Resistor_SMD:R_0402_1005Metric | 13-RC0402FR-135K6LCT-ND | RC0402FR-135K6L
 | 3 | R32, R40, R66 | 402K | Resistor_SMD:R_0402_1005Metric | YAG3151CT-ND | RC0402FR-07402KL
 | 3 | R33, R46, R68 | 2k | Resistor_SMD:R_0402_1005Metric | YAG2303CT-ND | RT0402BRD072KL
 | 18 | R34, R37, R42, R45, R47, R50, R51, R54, R55, R56, R59, R60, R67, R69, R72, R73,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 | 1k | Resistor_SMD:R_0402_1005Metric | 311-1.00KLRCT-ND | RC0402FR-071KL
 | 2 | J1, J2 | Screw Terminal | bitaxe:7771-screw-terminal | 36-7771-ND | 36-7771
 | 1 | J3 | Conn_02x05_Odd_Even | Connector_PinHeader_2.54mm:PinHeader_2x05_P2.54mm_Vertical
 | 1 | J6 | Conn_01x06 | Connector_PinHeader_2.54mm:PinHeader_1x06_P2.54mm_Vertical
 | 1 | J7 | USB_C_Receptacle_USB2.0 | Connector_USB:USB_C_Receptacle_GCT_USB4105-xx-A_16P_TopMnt_Horizontal | 2073-USB4105-GF-ACT-ND | USB4105-GF-A
 | 2 | J8, J9 | Conn_01x04 | bitaxe:470531000 | WM4330-ND | 470531000
 | 1 | L1 | 8.2 uH | bitaxe:74438357082 | 732-11745-1-ND | 78438357082
 | 1 | L2 | 680nH | Inductor_SMD:L_Coilcraft_XAL1010-XXX | 2457-XAL1010-681MED-ND | XAL1010-681MED
 | 2 | SW1, SW2 | SWITCH-SPST | bitaxe:TL3340-switch | EG4627CT-ND | TL3340AF160QG
 | 1 | U1 | LMR54410 | Package_TO_SOT_SMD:SOT-23-6 | 296-LMR54410DBVRCT-ND | LMR54410FDBVR
 | 1 | U2 | RT9080-33GJ5 | bitaxe:RT9080-33GJ5 | 1028-1509-1-ND | RT9080-33GJ5
 | 1 | U3 | TPS546D24ARVFR | bitaxe:LQFN40-CLIP | 296-TPS546D24ARVFRCT-ND | TPS546D24ARVFR
 | 1 | U4 | MIC5504 | Package_TO_SOT_SMD:SOT-23-5_HandSoldering | 576-4879-1-ND | MIC5504-1.8YM5-TR
 | 1 | U5 | SN74AVC4T774 | Package_SO:TSSOP-16_4.4x5mm_P0.65mm | 296-24739-1-ND | SN74AVC4T774PWR
 | 1 | U6 | ESP32-S3-WROOM-1 | bitaxe:ESP32-S3-WROOM-1U | 1965-ESP32-S3-WROOM-1U-N16R8CT-ND | ESP32-S3-WROOM-1U-N16R8
 | 2 | U7, U8 | TMP1075 | bitaxe:SOT5X3-6_DRL_TEX | 296-TMP1075NDRLRCT-ND | TMP1075NDRLR
 | 1 | U9 | EMC2302 | Package_SO:MSOP-10_3x3mm_P0.5mm | EMC2302-2-AIZL-CT-ND | EMC2302-2-AIZL-TR
 | 6 | U10, U11, U16, U17, U23, U24 | AP7331 | Package_TO_SOT_SMD:TSOT-23-5 | AP7331-WG-7DICT-ND | AP7331-WG-7
 | 4 | U12, U13, U22, U25 | BM1366_mode1 | bitaxe:BM1366
 | 3 | U14, U19, U26 | 25MHz | bitaxe:O 25,0-JO32-B-1V3-1-T1-LF | 1908-O250-JO32-B-1V3-1-T1-LFCT-ND | O 25,0-JO32-B-1V3-1-T1-LF
 | 2 | U15, U21 | TLV3544 | Package_SO:TSSOP-14_4.4x5mm_P0.65mm | 296-45352-1-ND | TLV3544IPWR
 | 2 | U18, U20 | BM1366_mode0 | bitaxe:BM1366

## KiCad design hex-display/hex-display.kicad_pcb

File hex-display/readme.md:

# BitaxeHex display adapter board
This adapater board provides a connection from the BitaxeHex to a 
172x320 SPI interface ST7789 Drive OLED graphic display.  This is 
intended for use on the [bitaxeHex](https://github.com/skot/bitaxeHex).
Currently, the firmware to drive it has not been developed, so this is 
provided in order to facilitate that effort.

The cable to connect it is constructed with a pair of JST-GH 12-pin housings, and 
cables that run straight through.  

## Parts
- [172x320 OLED display](https://www.aliexpress.us/item/3256804691627769.html)
- [JST-GH 12-pin housing](https://www.digikey.com/en/products/detail/jst-sales-america-inc/GHR-12V-S/807824)
- [JST-GH pre-crimped wires](https://www.digikey.com/en/products/detail/jst-sales-america-inc/AGHGH28K305/6009450)

To construct the cable:
- qty 12 of the pre-crimped cables
- qty 2 of the JST-GH housings

Insert the cables into the housings with the locking pin facing the same direction (both towards you)

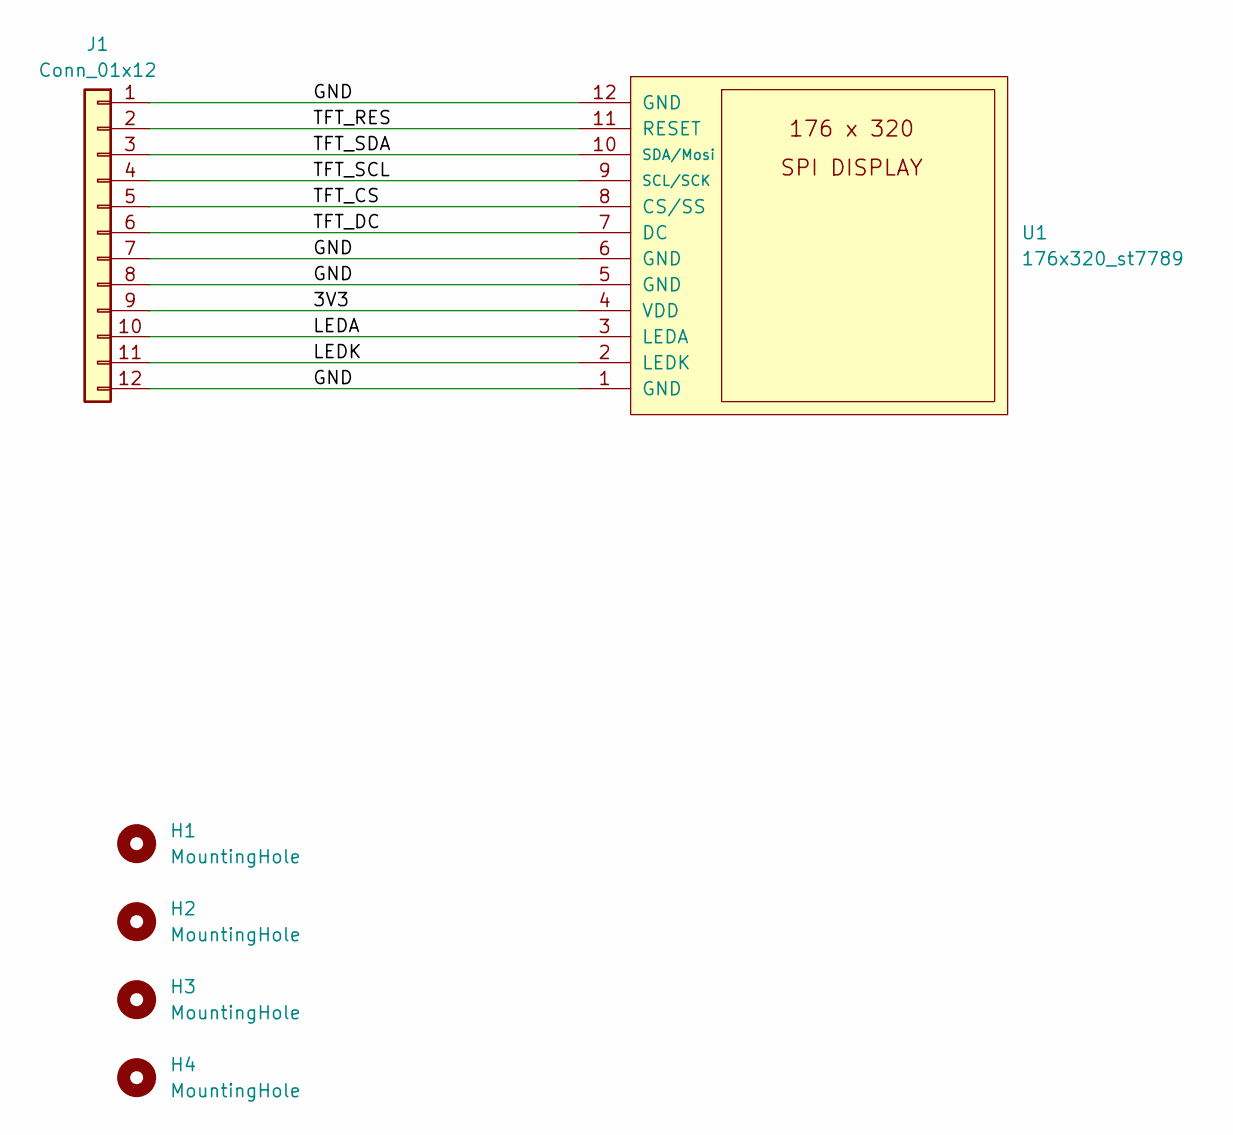
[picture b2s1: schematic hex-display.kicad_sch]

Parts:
H1, H2, H3, H4: MountingHole; 4mm_mounting
J1: Conn_01x12; JST_GH_BM12B-GHS-TBT_1x12-1MP_P1.25mm_Vertical
U1: 176x320_st7789; ST7789-176x320

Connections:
/3V3: J1.9, U1.4 (VDD)
/GND: J1.1, J1.7, J1.8, J1.12, U1.1 (GND), U1.5 (GND), U1.6 (GND), U1.12 (GND)
/LEDA: J1.10, U1.3 (LEDA)
/LEDK: J1.11, U1.2 (LEDK)
/TFT_CS: J1.5, U1.8 (CS/SS)
/TFT_DC: J1.6, U1.7 (DC)
/TFT_RES: J1.2, U1.11 (RESET)
/TFT_SCL: J1.4, U1.9 (SCL/SCK)
/TFT_SDA: J1.3, U1.10 (SDA/Mosi)

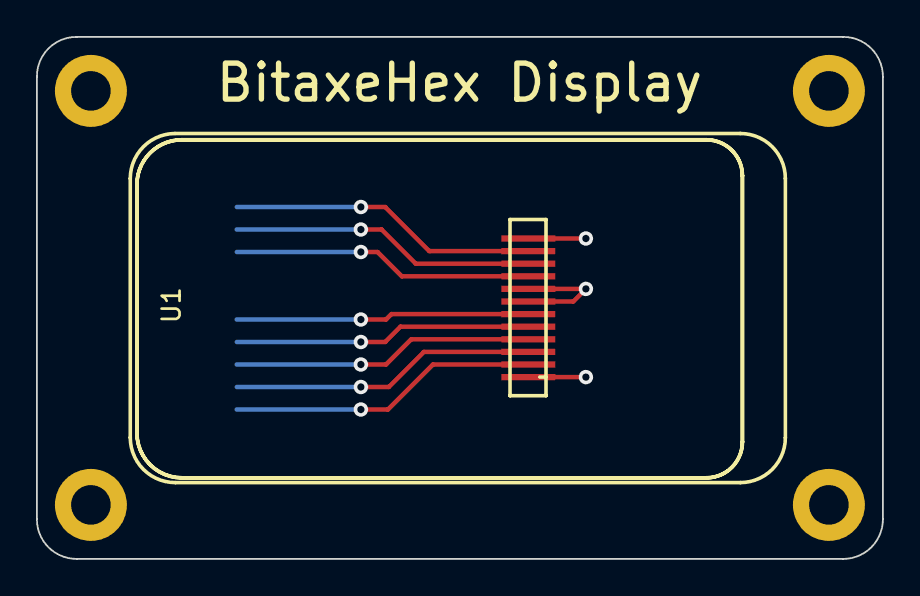
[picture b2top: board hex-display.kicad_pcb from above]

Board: 2 copper layers, 47.0 x 29.0 mm, 6 parts (1 on the bottom side), 9 nets.
